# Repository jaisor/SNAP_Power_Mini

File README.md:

# SNAP Mini Power Controller

Minimal solar charger and power distribution board, sized to power a mini handheld LoRa mesh node. It has solder pads for a 5 V solar panel, a 1S Li-ion battery, a load, an external switch that breaks the positive wire to the load, and an optional battery thermistor. A CN3163 charges the battery from the panel at up to 1 A, like the SD05CRMA module, with the same two status LEDs: red while charging, green when the battery is full. The LEDs are off until you bridge a solder jumper. A P-channel MOSFET protects everything from a battery connected backwards. 14.4 × 12.2 mm, no mounting holes: stick it down with foam tape or hot glue.

| Pads | Where | |
|---|---|---|
| **NTC** | top row, left | optional 10 kΩ battery thermistor (non-polar); joined by a copper link as delivered |
| **−OUT+** | top row, middle | load − and + (switched) |
| **SW** | top row, right | the two switch wires (non-polar) |
| **+SOL−** | bottom row, left | solar panel + and − |
| **+BAT−** | bottom row, right | battery + and − |

The charger feeds the battery directly, so the battery keeps charging with the switch off; the switch only cuts the load. All the − pads are connected.

**Status LEDs (JP1):** JP1 is the pair of tiny pads in the top-right corner of the parts area, right of the LEDs' resistors. It's open as delivered, so the LEDs are off and draw nothing. Bridge it with a blob of solder to turn them on; they then take about 2–3 mA from the panel while charging.

**Battery thermistor (NTC pads, JP2):** charging works without a thermistor. The two NTC pads are joined by a short strip of bare copper, which switches temperature sensing off. To use a thermistor, cut that strip with a knife and check with a meter that the pads are no longer shorted. Then solder a 10 kΩ B3950 NTC (taped to the cell) to the same pads. The charger then only charges between about 1 °C and 46 °C. A thermistor soldered on without cutting the strip is shorted out, so the sensing stays off.

## Dimensions

| | |
|---|---|
| Board outline | 14.4 × 12.2 mm (0.57 × 0.48 in), square corners |
| Board thickness | 1.6 mm |
| Overall thickness | about 3.4 mm with parts (the CN3163 is the tallest at up to 1.75 mm), plus your wires and solder |
| Wire pads | 1.4 × 1.5 mm, 2 mm apart centre to centre |
| Pad rows | centres 1.3 mm in from the top and bottom edges; pads start 0.55 mm from the edge |
| Top row, from the left edge | NTC 2.2 and 4.2 mm, OUT − 6.2 and + 8.2 mm, SW 10.2 and 12.2 mm |
| Bottom row, from the left edge | SOL + 1.25 and − 3.25 mm, BAT + 11.15 and − 13.15 mm |
| Mounting holes | none |

The width and height are also marked on the top and bottom pictures.

## Specifications

- Board: 14.4 × 12.2 mm, 1.6 mm FR-4, 2 layers, square corners (V-score panel friendly). No mounting holes
- Pads: 1.4 × 1.5 mm SMD at 2 mm pitch, for wires up to ~24 AWG
- Current: 1 A maximum on any net
- Solar input: 4.4–6 V. **Absolute maximum 6.5 V**: use a 5 V panel whose open-circuit voltage stays under 6.5 V. No reverse-polarity protection on the panel input.
- Battery reverse-polarity protection: AO3401A P-MOSFET in the battery + line, gate to GND. A correctly connected cell turns it fully on (~60 mΩ, both directions, so charging works through it); a reversed cell leaves it off and nothing on the board sees the wrong polarity.
- Charging: 4.2 V float, 0.99 A maximum (R1 = 1.2 kΩ). The CN3163 lowers the current by itself when the panel sags toward 4.4 V or the chip reaches ~130 °C. On a board this small it will run hot and throttle at full current, which is normal.
- Battery temperature (optional): 10 kΩ B3950 NTC on the NTC pads, with the copper link between them cut. Charging is suspended outside ~1–46 °C (4.7 kΩ / 47 kΩ divider from the panel input). With the link intact the divider draws ~1 mA from the panel while the sun is up.
- Status LEDs: red = charging, green = charge complete. Enabled by bridging JP1 (open by default). They're powered from the panel, so they're off without sun.
- Parts: CN3163 (eSOP-8), AO3401A (SOT-23), 1.2 kΩ 1 %, 2 × 10 µF 10 V (0603); red and green LEDs, 2 × 1 kΩ, 4.7 kΩ and 47 kΩ 1 % (0402). Top side only

## Schematic

## Back

The back carries the short name (SNAP Power Mini), the limits and a warning:

| Printed | Meaning |
|---|---|
| CHECK POLARITY | Check + and − on every wire before connecting. The battery input survives a reversed cell; the solar input and the load output have no protection |
| SOL MAX 6V 1A | Solar panel: 6 V and 1 A; see the limits under [Safety](#safety) |
| OUT MAX 1A | Load: 1 A maximum |
| AS IS NO WARRANTY | See [Safety](#safety) and the [licence](#license) |

Under the text, the back is a ground plane with two jumpers (battery + up to the charger's sense pin, and the panel input round to the LED jumper) and six thermal vias under the CN3163.

## Fabrication

The package is generated into `output/fab/`. It isn't tracked in git; regenerate it with the commands in `CLAUDE.md`.

| File | Contents |
|---|---|
| `SNAP_Power_Mini_v1.0_gerbers.zip` | Upload this to the board house: Gerbers incl. solder paste, drill files, job file. 2 layers, 1.6 mm, 1 oz copper |
| `SNAP_Power_Mini_v1.0_BOM.csv` | BOM in JLCPCB format with LCSC part numbers for every line |
| `SNAP_Power_Mini_v1.0_CPL.csv` | Pick-and-place file, top side only, same coordinates as the Gerbers |
| `FAB_NOTES.txt` | Order settings and assembly cautions |

All parts are in JLCPCB's Basic library except the CN3163 (C559031) and the two 0402 LEDs. Those three are Extended parts, which add a loading fee per part type, and none of them has a Basic equivalent that fits this board. The AO3401A is C15127. Check the rotation of U1 and Q1 and the polarity of the LEDs in the assembler's preview before ordering. The wire pads and the LED solder jumper aren't parts, so they're not in the BOM or placement file.

## Safety

This is an experimental design for charging a lithium-ion cell. It's provided as is, with no warranty, and hasn't been certified to any safety standard. If you build it, you're responsible for:

- Assembling it correctly and checking polarity before connecting a panel, a cell or a load. Q1 protects against a reversed cell on the battery pads, but the solar input and the load output have no protection, and a battery soldered to the solar pads is not covered either.
- Using a protected cell or a separate protection circuit. The CN3163 charges the cell but doesn't protect it from over-discharge or short circuits, and the board has no fuse.
- Fusing, wiring and an enclosure suited to where the node is used, including outdoor heat and moisture.
- Not using it where a failure could hurt someone or damage property.

**Limits**, also printed on the back of the board:

| | Limit | Set by |
|---|---|---|
| Battery | One Li-ion or LiPo cell (1S), charged to 4.2 V | The CN3163's fixed charge voltage |
| Panel voltage | 6 V in use, and never above 6.5 V open-circuit. Use a 5 V panel | The CN3163's absolute maximum rating; nothing sits between the pads and the chip |
| Panel current | The charger draws 1 A at most. A panel that can supply more is fine if its voltage is within the limit | R1 (charge current) |
| Load on OUT | 1 A | The tracks and vias |

**No warranty:** the board is provided as is, and you use it at your own risk. Where the law allows a limit, liability for a board you bought is limited to the price you paid for it. The design itself is covered by the disclaimer in the [licence](#license).

## Regenerating the design

The schematic and board are generated by the scripts in `tools/`; see `CLAUDE.md` for the commands.

## License

Copyright 2026 Jordan Marinov (JaisorGadgets).

The hardware design (schematic, board, symbol and footprint libraries) and its documentation, including the images in `docs/images/`, are licensed under the [CERN Open Hardware Licence Version 2 – Permissive](LICENSE) (CERN-OHL-P-2.0). You may redistribute and modify them, and make and sell products from them, under the terms of the licence. They are distributed WITHOUT ANY EXPRESS OR IMPLIED WARRANTY, INCLUDING OF MERCHANTABILITY, SATISFACTORY QUALITY AND FITNESS FOR A PARTICULAR PURPOSE. See section 5 of the licence for the disclaimer and limitation of liability.

The scripts in `tools/` are licensed under the [MIT License](tools/LICENSE).

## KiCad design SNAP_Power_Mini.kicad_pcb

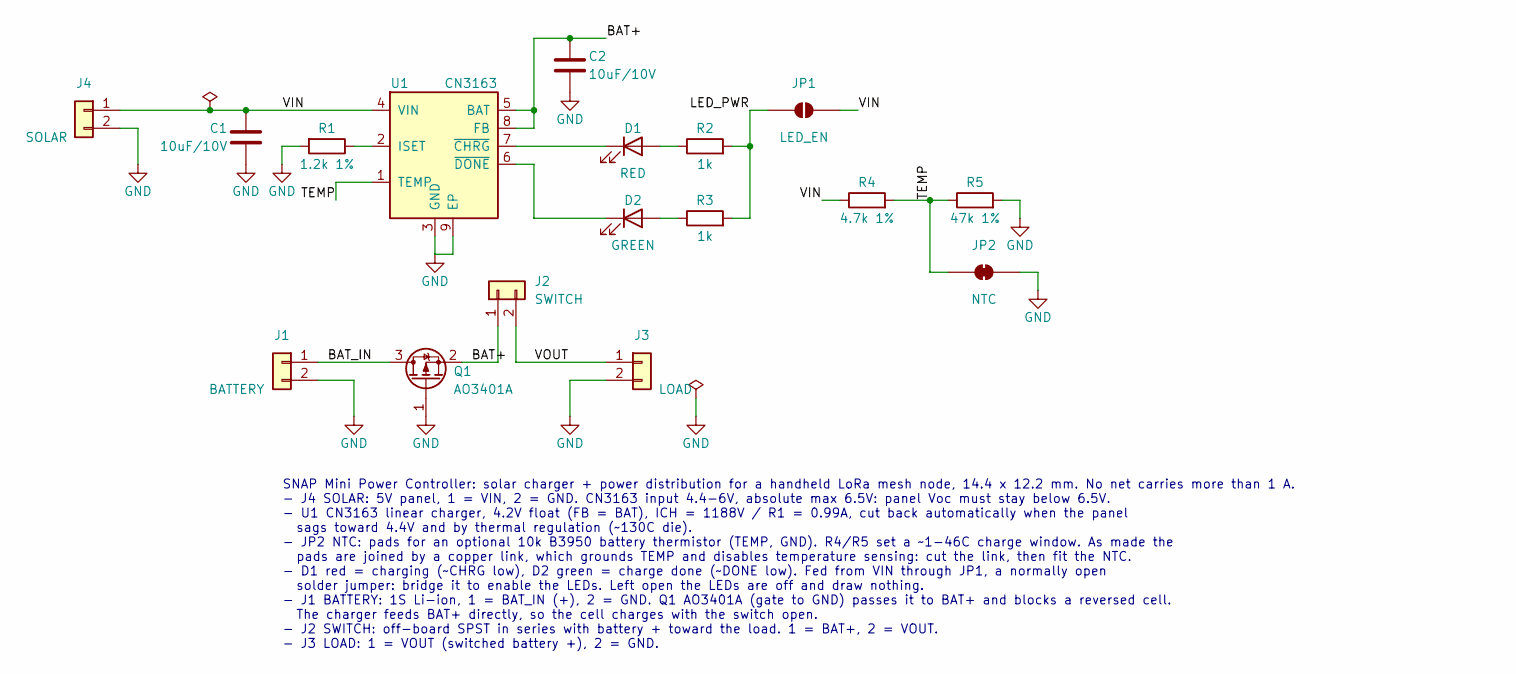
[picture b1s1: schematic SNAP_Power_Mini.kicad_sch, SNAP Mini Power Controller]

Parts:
C1, C2: 10uF/10V; C_0603_1608Metric
D1: RED; LED_0402_1005Metric
D2: GREEN; LED_0402_1005Metric
J1: BATTERY; WirePad_1x02_SMD_1.4x1.5mm_P2.0mm
J2: SWITCH; WirePad_1x02_SMD_1.4x1.5mm_P2.0mm
J3: LOAD; WirePad_1x02_SMD_1.4x1.5mm_P2.0mm
J4: SOLAR; WirePad_1x02_SMD_1.4x1.5mm_P2.0mm
JP1: LED_EN; SolderJumper-2_P0.9mm_Open_Pad0.6x0.8mm
JP2: NTC; WirePad_1x02_SMD_1.4x1.5mm_P2.0mm_Bridged
Q1: AO3401A; SOT-23
R1: 1.2k 1%; R_0603_1608Metric
R2, R3: 1k; R_0402_1005Metric
R4: 4.7k 1%; R_0402_1005Metric
R5: 47k 1%; R_0402_1005Metric
U1: CN3163; SOIC-8-1EP_3.9x4.9mm_P1.27mm_EP2.41x3.3mm

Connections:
/BAT+: C2.1, J2.1, Q1.2 (S), U1.5 (BAT), U1.8 (FB)
/BAT_IN: J1.1, Q1.3 (D)
/LED_PWR: JP1.1 (A), R2.2, R3.2
/TEMP: JP2.1 (A), R4.2, R5.1, U1.1 (TEMP)
/VIN: C1.1, J4.1, JP1.2 (B), R4.1, U1.4 (VIN)
/VOUT: J2.2, J3.1
GND: C1.2, C2.2, J1.2, J3.2, J4.2, JP2.2 (B), Q1.1 (G), R1.2, R5.2, U1.3 (GND), U1.9 (EP)
unnamed: D1.2 (A), R2.1
unnamed: D1.1 (K), U1.7 (~CHRG)
unnamed: D2.2 (A), R3.1
unnamed: D2.1 (K), U1.6 (~DONE)
unnamed: R1.1, U1.2 (ISET)

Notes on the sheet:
SNAP Mini Power Controller: solar charger + power distribution for a handheld LoRa mesh node, 14.4 x 12.2 mm. No net carries more than 1 A. - J4 SOLAR: 5V panel, 1 = VIN, 2 = GND. CN3163 input 4.4-6V, absolute max 6.5V: panel Voc must stay below 6.5V. - U1 CN3163 linear charger, 4.2V float (FB = BA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

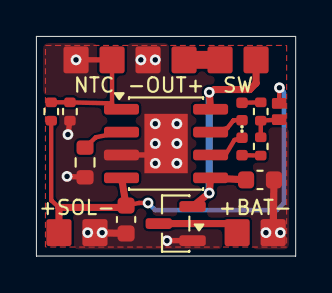
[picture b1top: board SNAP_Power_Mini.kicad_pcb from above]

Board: 2 copper layers, 14.4 x 12.2 mm, 17 parts (0 on the bottom side), 12 nets.
